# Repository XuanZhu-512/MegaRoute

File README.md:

# MegaRoute — PCB Routing Algorithm Reimplementation

A research and reimplementation project based on **MegaRoute: Universal Automated Large-Scale PCB Routing Method with Adaptive Step-Size Search** (DATE 2025).

## 1. Overview

**当前架构决策（2026-11-16）：** 正式 benchmark 统一输入/输出 `.kicad_pcb`，保留配套项目规则；MegaRoute、Freerouting、KRT 共用锁定版本的外部 KiCad 评测。几何 IR 仅作为自研算法内部接口，提供 KiCad -> IR 和原板模板上的 IR 结果回写契约。当前已落地架构契约、案例快照及版本探测，转换器和正式外部评测仍待实现。详见 [`pcb-bench/docs/ARCHITECTURE.md`](pcb-bench/docs/ARCHITECTURE.md)。下文较早规划中的 JSON 输入与内部 DRC 指标仅用于几何核心开发测试，不再定义跨算法正式评测口径。

This project aims to study, reconstruct, and independently implement the MegaRoute algorithm, a universal automated PCB routing method designed for large-scale printed circuit boards (PCBs).

MegaRoute combines adaptive step-size search, shape-based obstacle detection, and routing optimization to achieve high routing completion rates while maintaining strict Design Rule Check (DRC) compliance.

**Original Paper:**

- **Title:** MegaRoute: Universal Automated Large-Scale PCB Routing Method with Adaptive Step-Size Search
- **Authors:** Haiyun Li, Jixin Zhang
- **Conference:** DATE 2025
- **DOI:** [10.23919/DATE64628.2025.10993225](https://doi.org/10.23919/DATE64628.2025.10993225)
- **IEEE Xplore:** https://ieeexplore.ieee.org/document/10993225

## 2. Research Objectives

- Develop an end-to-end, universal router for entire PCBs, including mainboards with thousands of nets, heterogeneous components, and multiple layers.
- Achieve nearly complete connectivity and DRC-compliant final routing while keeping computation practical at large scale.
- Combine the path-search capability of grid-based routing with precise geometric obstacle modeling, avoiding fixed-grid precision errors and overly restricted search spaces.
- Minimize wire length and via count while maximizing routability. The paper expresses this as `max R(P) - W(P) - V(P)`, subject to `P` satisfying design rules, given layout `L`, netlist `N`, and rules `D`.

For this reimplementation, the objective is to reconstruct and evaluate these mechanisms against the paper's reported results. Differential-pair support is identified as future work in the paper, not an established capability of MegaRoute.

## 3. Algorithm Overview

The workflow is `layout + netlist + design rules -> initialization -> route generation with geometric obstacle detection -> iterative routing optimization -> final routes`

**Adaptive step-size search.** Each net is decomposed into two-terminal searches over nodes `(x, y, z)`, where `z` is the layer. Five exploration operations generate candidates (Figure 4, Equations 2-7):

1. **Obstacle-aware exploration:** expand in eight planar directions. With wire width `w`, nearest-obstacle distance `d`, and parameter `beta`, use step `delta = w` when `d <= beta * w`, otherwise `delta = beta * w`.
2. **Axis alignment:** align with the target along the axis with the smaller absolute displacement, when both coordinate displacements are nonzero.
3. **Diagonal alignment:** adjust one coordinate so the remaining target direction is 45 degrees, when `0 < abs(abs(dx) - abs(dy)) < delta`.
4. **Layer change:** consider nodes at the same planar coordinates on other layers, using vias.
5. **End connection:** connect directly when the target is on the same layer, closer than the step size, and aligned horizontally, vertically, or diagonally.

**Shape-based obstacle detection.** Represent pins as polygons/circles, boundaries and wires as line geometry, and vias as circles. Compute geometric clearances with wire widths and radii included. Same-layer shapes belonging to different nets obstruct one another; boundaries and restricted areas also constrain routing. Each proposed wire is checked against existing geometry, and a via requires clearance checks across the layers it penetrates.

**Routing optimization.** Prioritize candidates using wire-length cost, DRC-violation cost, and layer-change cost. The A*-like length heuristic is `h = max(abs(dx), abs(dy)) + (sqrt(2) - 1) * min(abs(dx), abs(dy))`. Suppress new nodes within `d_min` of an existing node to limit search density. Iterative rerouting increases the DRC penalty using `alpha_i = L * (f(i) - f(0)) / (f(2*mu) - f(0))`, where `f(x) = 1 / (1 + exp(-k*(x-mu)))`.

Intermediate iterations can tolerate violations at a penalty; DRC-free results refer to the reported final outputs. The paper mentions path refinement but does not provide a separate detailed refinement algorithm.

### 3.1 Algorithm Specification（实现前优先冻结）

下文 **[P]** 表示论文明确给出的机制，**[E]** 表示为形成可执行规范而补充的工程约定。工程约定不代表作者实现；所有算法尚待实现。

#### 搜索状态与节点管理

**[P]** 每个网络分解为若干两端路径问题。位置状态为 `n=(x,y,z)`，起点 `s`、终点 `t`，`z` 是铜层索引。令 `dx=t.x-x`、`dy=t.y-y`、`a=abs(dx)`、`b=abs(dy)`、`q=abs(a-b)`。搜索通过当前节点到候选节点的边构成路径。论文规定：新节点距已有节点小于 `d_min` 时抑制新节点。

**[E]** 搜索上下文保存 net ID、线宽、目标、规则、不可变的本次搜索障碍快照；记录保存 `position, heading, g_length, g_drc, g_via, parent, operation, insertion_id`。`heading` 是当前层的八方向入射方向，起点和换层后的第一段为未定。同位置、同层、不同入射方向是不同状态，避免一个到达挡住另一个合法的 45° 到达。每次两端搜索清空 open/closed 和节点索引。候选先执行规则检查，再进行去重/抑制；同位置且同入射方向的较低累计代价可更新并重新入队。密度查询比较同层的所有已采样位置，不按入射方向过滤，条件为欧氏距离 `< d_min`；目标连接不受密度抑制。同一位置的不同入射方向作为同一几何采样点的不同搜索状态保留。这是为转角约束补充的工程状态管理，不是论文给出的完整状态机。队列按 `(F, h, insertion_id)` 升序，同分时固定插入顺序：八方向按东起逆时针、轴对齐、对角对齐、层号升序换层、末端连接。

终点从优先队列弹出后回溯路径；起终点相同直接判为已连接。open 耗尽仅表示在本搜索策略下未找到路径，不证明连续空间不可达。自适应采样和密度抑制不保证完备性或全局最优性。同一层相邻段的转角不超过 45°（内角至少 135°）。过孔不继承上一层的平面入射方向，下一层的第一段重新自由选向。已有同网焊盘或过孔内部的汇接不作为两条独立路径之间的平面转角；纯线段接头仍检查转角。此角度检查是工程补充，论文未给出分支、接入与细化的完整算法。

#### Adaptive Step Size 与五种探索

**[P, Eq. 2]** 当前网络线宽为 `w>0`，最近障碍距离为 `d_obstacle`：

```text
delta = w         if d_obstacle <= beta*w
        beta*w    if d_obstacle >  beta*w
```

它是两档步长，而非随距离连续插值。**[E]** 论文未精确定义该距离的参考点及是否扣除规则间距；首版取当前节点到同层异网实体铜、板边及禁布区的最小几何距离，不扣除当前线宽半径或 clearance，位于障碍内部时为 0，无障碍时为正无穷。该距离仅控制采样密度，不能替代整段 DRC。记录为 `obstacle_distance_mode=point_to_shape`。

| 探索 | 数学规则 [P] | 前提及实现注意 |
| --- | --- | --- |
| Obstacle-aware，Eq. 3 | `{(x+u,y+v,z) : (u,v) in {-delta,0,delta}², (u,v)!=(0,0)}` | 共八个候选；对角边长度为 `sqrt(2)*delta`，不是 `delta` |
| Axis alignment，Eq. 4 | `a<b` 时 `(x+dx,y,z)`；否则 `(x,y+dy,z)` | 仅当 `a>0 AND b>0`；相等时走 y 分支；论文没有要求该对齐边短于 delta |
| Diagonal alignment，Eq. 5 | `a<b` 时 `(x,y+q*sign(dy),z)`；`b<a` 时 `(x+q*sign(dx),y,z)` | 仅当 `0<q<delta`；调整后到目标的剩余方向为 45° |
| Layer change，Eq. 6 | `{(x,y,z') : z' in Z, z'!=z}` | 候选包括所有其它铜层；[E] 再按允许过孔类型和实际贯穿层筛选，不能默认只检查起止层 |
| End connection，Eq. 7 | 候选为 `t`：`dy=0` 时 `(x+dx,y,z)`；`dx=0` 时 `(x,y+dy,z)`；`a=b` 时 `(x+dx,y+dy,z)` | 要求 `z=t.z`、距离 `<delta`，且满足上述方向之一；[E] 距离采用 `sqrt(dx²+dy²)`，原文未明确范数 |

**[E]** 以上是候选生成规则，不保证候选可接受。所有平面候选，包括长轴对齐边，都要检查整条带宽线段；换层检查完整过孔。相等判断使用几何容差，候选落到目标时使用目标的原始坐标，不累积舍入误差。

#### Heuristic 与 Cost Function

**[P, Eq. 8]** 长度代价由起点到当前节点的历史线长与目标估计距离组成：

```text
h(n,t) = max(a,b) + (sqrt(2)-1)*min(a,b)
```

**[P, IV-C.1]** DRC 代价反映违规数量；换层代价通常与过孔直径成正比。论文没有给出三者相加的完整公式、单位归一化、权重数值或违规累计规则。

**[E]** 首版冻结以下组合（不是论文原公式），几何仍存 mm，成本长度单位 `u_cost=0.0254 mm`：

```text
g_length = sum(planar_edge_length / u_cost)
g_drc    = sum(number_of_unique_violation_keys_for_each_edge)
g_via    = sum(diameter_of_inserted_via / u_cost)
F_i(n)   = g_length + h(n,t)/u_cost + alpha_i*g_drc + lambda_v*g_via
lambda_v = 1
```

每条边内按 `(rule, obstacle_id, layer)` 去重；跨边重复遇到障碍仍可重复计费，因此此搜索代价不等于最终全板 DRC 数量，也会受路径分段影响。层变不增加平面线长；首版每个层变动作计一次过孔成本，最终物理过孔数另行去重。几何硬约束违规直接拒绝；仅异网铜间距违规可作为软冲突。严格模式下 `g_drc=0`，一切间距违规拒绝。不得通过米/mm 单位切换而无声改变代价权重。

#### Logistic DRC Penalty

**[P, Eq. 9]**

```text
f(x)    = 1 / (1 + exp(-k*(x-mu)))
alpha_i = L * (f(i)-f(0)) / (f(2*mu)-f(0))
L=200, k=0.4, mu=10; maximum iterations=20
```

由公式可得 `alpha_0=0`、`alpha_10=100`、`alpha_20=200`。**[E]** 原文未说明首次迭代编号；首版总共最多 20 次布线遍历，编号 `i=1..20`（`alpha_1` 约为 1.79），不额外运行第 0 轮。迭代中 alpha 固定；跨轮重建搜索状态。迭代参数改变需验证分母非零，并记录实际权重序列；不擅自把公式延伸到 `i>20` 后仍称最大权重为 L。

#### 重布线策略

**[P, IV-C.2]** 论文说明顺序布线会挤占后续网络空间，采用多轮布线，并用 Logistic 逐步增大违规惩罚。没有明确给出拆线集合、网络次序、失败回滚、历史拥塞项或完整伪代码；不能直接将 Pathfinder 的所有机制视为 MegaRoute 已定义内容。

**[E]** 首版采用以下可替换的确定性策略 `reroute_policy=conflict_nets_v1`：

1. 输入已有同网铜先构成连通分量；使用端点欧氏距离的最小生成树分解连接需求，同分按端点 ID；网络按需求总长度降序、net ID 升序排列。焊盘首版采用中心作为搜索接入点，中心须在铜内，非凸形状否则需显式接入点。
2. 第 1 轮布线全部待连接网络。每轮结束独立检查连通性和 DRC；未完成网络及所有冲突涉及的可编辑网络构成下一轮集合。板框、焊盘、固定铜、禁布区不可拆除。
3. 下一轮先同时移除选中网络的全部新增铜并更新索引，再按固定顺序重新生成剩余连接需求、逐个布线；未选网络保留。失败网络不恢复旧违规走线，保留部分成果并记录失败原因。
4. 每轮保存工作快照、最佳零违规快照及最佳诊断快照。合法解按 `(完成连接数降序, WL升序, VC升序)` 比较；诊断解按 `(完成连接数降序, DRC升序, WL升序, VC升序)` 比较。预算用尽返回合法解（可为空的新增路线）及独立标记的诊断解，不混用指标。
5. 全部需求连通且 DRC=0 时提前终止；否则直到 20 轮或预算耗尽。不宣称 Logistic 必然消除所有违规。路径细化默认关闭，后续独立评估。

### 3.2 Geometry & DRC Specification

**[P, IV-B，pp. 4-5]** 引脚用圆或多边形，走线/边界用线几何，过孔用圆；对象关联网络和层。异网且同层对象互为障碍，过孔必须检查其穿越的各层。以下实体定义、容差及检查覆盖范围是 **[E]**，将原文描述补全为平台规范。

#### 数学表示与层跨度

设圆盘 `D(c,r)={p:||p-c||<=r}`，线段 `S(a,b)={a+t(b-a):0<=t<=1}`。

| 对象 | 实体表示与属性 |
| --- | --- |
| 圆焊盘 | `D(c,r)`，net ID、pad ID、铜层集合 |
| 多边形焊盘 | 简单闭合多边形的填充区域 P；内孔显式存储；拒绝自交轮廓 |
| 走线 | 胶囊体 `S(a,b) ⊕ D(0,w/2)`，圆端帽，所属单一铜层；折线为各段实体并集 |
| 过孔 | 中心 c、外铜半径 R、钻孔半径 r、起止层及每层铜形状；间距检测保守使用外圆盘，钻孔与镀层连通属性独立保存 |
| 板框/开孔 | 可布线区域 B（外多边形减内部开孔）；边界为有限线段，不能当无限直线 |
| 禁布区 | 闭合区域 K 和适用铜层集合，与 net 无关；无网络铜按障碍处理，不视为同网 |

铜层 `Z={0,...,m-1}` 按 stackup 排序；丝印、阻焊不参与路由层编号。实体 A、B 仅在 `layers(A) ∩ layers(B)` 上检查铜间距。通孔穿越全部铜层，即使搜索仅从层 0 到层 1 也必须检查其它层；盲埋孔使用真实起止层的连续跨度，只能使用输入允许的 via type。首版生成器只用通孔；未声明的层跨度或 via 类型应报错。平面同网铜相交建立连通关系，跨层只通过明确的镀通孔/过孔连通，不能仅凭 x/y 相同判定连接。

#### Clearance 和精确窄相检查

定义 `dist(A,B)=min ||a-b||`（a、b 属于各自闭合实体）；相交或包含时为 0。规则间距 `c_req>=0` 使用 net-class 对称配对规则，未设置配对规则时取两网要求的较大值。数值容差默认 `eps=1e-6 mm`，与 `d_min=0.0254 mm` 完全独立。

| 对象对 | 几何间距计算（未截断量为负代表重叠） |
| --- | --- |
| 圆-圆 | `g=||c1-c2||-r1-r2` |
| 圆-走线 | `g=dist(c,S)-r-w/2`，投影参数钳制到 `[0,1]`，含端点和退化线段 |
| 走线-走线 | `g=dist(S1,S2)-(w1+w2)/2`，先检查交叉，再求端点到线段距离最小值 |
| 多边形-圆 | `g=dist(c,P)-r`；先执行点在填充区域内判断，不能只测轮廓边 |
| 多边形-走线 | `g=dist(S,P)-w/2`；线段与实体相交/包含时底层距离为 0 |
| 多边形-多边形 | `g=dist(P,Q)`；相交、包含先判为 0，否则取边对距离最小值 |
| 铜-板边/开孔 | 先要求整个铜实体包含于 B，再要求到 `boundary(B)` 的距离不小于板边间距 |
| 铜-禁布区 | 不得与 K 相交；若规则另设退让距离，还需 `dist(copper,K)>=c_keepout` |

铜间距使用 `max(0,g)`，其中负值不作为通用穿透深度。间距 `<c_req-eps` 判违规；落在容差带内记录边界诊断。异网实体相交或接触另报短路，即使 `c_req=0` 也不能仅靠非负距离判合格。同网间距豁免不豁免板边、禁布、线宽、钻孔等约束。数值上无法确定的临界几何应保守拒绝候选并报告，不能默认合法。

实现采用扩张 AABB / R-tree 的宽相过滤后进行上述窄相几何判断；查询框必须覆盖线宽半径和最大相关间距。这里“精确”表示检查实际实体而非栅格占用，并不宣称双精度运算具有任意精度算术保证。最终全板检查独立枚举对象关系，小案例以全量对象对检查对照索引结果，覆盖相切、包含、退化线段、长边穿障碍及过孔中间层冲突。

#### 内部 DRC 覆盖与局限

首版支持：异网铜短路/间距、最小线宽、板边/孔洞间距、禁布区、过孔尺寸/铜环下限 `(R-r)`、合法层跨度及端点连通性。断路独立计入未完成连接，不同时计作几何 DRC。固定输入的违规单列，新增或由新增铜参与的违规另列，总体零违规必须两者皆为零。

首版不支持：差分对、等长/时延、阻抗、信号完整性、回流路径、阻焊/丝印、热焊盘、自动铺铜、钻孔到钻孔/铜的完整制造约束、完整角度规则及厂商专有 DRC。圆弧/样条需后续受控转换或明确拒绝；不能静默离散化后声称原始几何精确。过孔外圆盘模型对孔内铜关系是保守近似。报告必须带 `supported_rules`、`unsupported_features` 和容差；内部 `DRC=0` 只表示受支持规则下通过。论文用 EasyEDA 评价，平台结论须在后续真实数据阶段交叉验证。

## 4. Development Environment

| Item | Reported configuration |
| --- | --- |
| Implementation language | C++ |
| Compiler/toolchain | mingw64 (MinGW64); compiler version and flags not specified |
| Operating system | Windows 11 |
| CPU / RAM | Intel Core i9-13900K / 64 GB |
| Input format | EasyEDA Pro project format; its conversion tool exports inputs for other routers |
| Evaluation tool | EasyEDA; reference [20] identifies EasyEDA Pro Edition 2.1.25 |
| Search parameters | `beta = 5`, `d_min = 1 mil` (0.0254 mm) |
| DRC optimization | `L = 200`, `k = 0.4`, `mu = 10`; maximum 20 iterations |

The paper does not specify a C++ standard, build system, third-party geometry libraries, parallelization settings, or an exact build command. These remain implementation decisions for this project.

**Evaluation dataset:** 101 real-world designs from OSHWHub, spanning 7-1564 nets, 2-6 layers, 14-3161 pins, 6-2326 connections, and 42-37845 mm². There are 93 designs below 1000 pins and 8 designs with 1011-3161 pins. Although the abstract uses broader wording, Section V-A specifies 101 designs for the reported experiment.

## 5. Project Structure

**当前实现入口：** [`pcb-bench/README.md`](pcb-bench/README.md)。代码已放在 `pcb-bench/`，提供 C++17 CLI、标准 JSON、几何/DRC、固定步长与严格 DRC 自适应搜索、测试及 Python 实验工具。下面的目录是完整目标设计；已实现范围、工程差异和待办以子目录 README 为准，Logistic 多轮重布线已接入，默认后端使用 `configs/megaroute.json`。

以下为**待实现的项目设计**，并非已经存在的代码或论文指定的工程结构。仿真平台定位为 PCB 几何布线、DRC 检查和算法实验平台，不包含电磁场或信号完整性仿真。先用合成电路板和手写标准数据跑通流程，再接入真实设计；EasyEDA 文件解析、转换和回写脚本暂不实现。

### 5.1 技术方案与模块边界

- **算法核心：** C++17 + CMake + Ninja，优先支持 Windows / MinGW64；以独立库形式实现几何、搜索、重布线和评估，命令行程序负责组织运行。先保证单线程结果可复现，性能优化依据 profiling 再推进。
- **数据与配置：** 采用版本化 JSON，计划使用 nlohmann/json；几何索引计划使用 Boost.Geometry R-tree，精确距离与碰撞判断封装在独立模块内。依赖版本在搭建阶段锁定，不依赖运行时自动下载。
- **实验与展示：** Python 负责合成案例、批量实验和统计；先用 Matplotlib 展示分层走线、过孔、障碍物及 DRC 标记，通过 JSON/事件日志回放算法过程。展示端读取核心输出，不另写一套布线逻辑；无界面模式也能完成全流程。
- **测试：** CTest + Catch2 验证 C++ 核心，Python 实验工具按需测试。内部 DRC 是平台定义规则下的检查结果，不能直接替代后续 EasyEDA 外部验证。

### 5.2 目标目录

数据统一位于与 `pcb-bench/` 并列的 `dataset/`：`dataset/test/` 存放 KiCad 测试板，`dataset/geometry-fixtures/` 存放内部 JSON 几何夹具。以下为程序模块目标，命令示例从 `pcb-bench/` 执行。

```text
MegaRoute/
├── README.md
├── CMakeLists.txt                 # 核心库、CLI、测试目标
├── CMakePresets.json              # 开发/发布构建配置
├── pyproject.toml                # 实验和可视化工具依赖
├── include/megaroute/            # 对外类型、路由器和适配器接口
├── src/
│   ├── model/                    # Board、Layer、Pad、Net、Rules、Route
│   ├── geometry/                 # 图形距离、碰撞、分层空间索引
│   ├── drc/                      # 候选检查与最终全板检查
│   ├── routing/                  # 两端连接分解、搜索状态、五类扩展、代价
│   ├── optimization/             # 冲突记录、拆线重布、惩罚调度、路径简化
│   ├── simulation/               # 场景生命周期、快照、事件、停止条件
│   ├── evaluation/               # 连通性、线长、过孔、DRC、运行开销
│   └── io/                       # 标准 JSON 读写与适配器契约
├── apps/                         # megaroute_cli 入口
├── schemas/                      # board、config、result、event 的 JSON schema
├── adapters/
│   └── easyeda/                  # 仅接口说明与映射约定；暂不写解析脚本
├── configs/                      # 基线、完整算法、消融、规模实验配置
├── tools/
│   ├── generate_cases/           # 标准格式合成板生成
│   ├── experiments/              # 批量运行、超时管理、汇总
│   └── visualization/            # 分层显示、搜索与重布线回放
├── tests/
│   ├── unit/                     # 几何、规则、候选、代价和惩罚函数
│   ├── integration/              # 输入到最终布线的确定性案例
│   └── fixtures/                 # 合法、非法、不可达及边界条件输入
├── docs/                         # 数据协议、算法映射、复现假设记录
└── results/                      # 每次运行的配置、走线、日志与指标
```

`build/` 和 `results/` 的生成内容不纳入版本控制；小型测试夹具与实验配置纳入版本控制。核心依赖方向为 `CLI / simulation -> routing / optimization -> model / geometry / drc`，评估读取模型和结果；核心不得依赖展示工具或 EasyEDA 数据字段。

### 5.3 标准数据与 EasyEDA 预留接口

标准输入 `BoardDocument` 包含 `schema_version`、单位、板框及开孔、铜层顺序、焊盘形状与所属网络、网络端点、禁布区、固定走线和过孔、线宽/间距/过孔规则。坐标统一为 mm，明确原点和轴方向；内部使用双精度几何并配置数值容差，`d_min` 与数值容差独立，不能将搜索节点抑制等同于固定网格量化。焊盘与过孔必须注明占用层/层跨度。

初期规则覆盖线宽、异网铜间距、板边间距及过孔铜环/孔径/层跨度；未支持的规则或图形必须报告，不能静默丢弃。导入时校验 ID 唯一性、网络引用、层引用、几何合法性和单位。固定输入中的违规项单独记录，避免与新增走线违规混淆。

| 接口契约（计划） | 职责 |
| --- | --- |
| `IBoardImporter.load(path, options) -> ImportResult` | 返回标准板数据、来源 ID 映射、警告及不支持项；当前仅实现标准 JSON importer |
| `IRouter.route(board, config, observer) -> RoutingResult` | 接收与 EDA 无关的模型；返回走线、未完成连接、终止原因和统计 |
| `IRouteExporter.save(result, path, options)` | 当前仅输出标准 JSON；保留未来 EasyEDA 导出扩展点 |
| `IRoutingObserver.on_event(event)` | 记录搜索、提交走线、拆线、迭代完成等事件；支持关闭或采样以控制开销 |

EasyEDA 适配器后续负责单位、层、图形、网络和规则到上述模型的映射；保留 `source_id` 与扩展元数据以便追溯和未来回写。现阶段调用未实现的 EasyEDA 适配器应明确返回 `unsupported_format`，不以空板或模拟成功替代。

一次运行输出 `board.json`（规范化输入）、`config.json`（实际生效参数）、`routes.json`、`metrics.json` 和可选 `events.jsonl`。记录随机种子、代码版本、编译配置、机器信息、输入摘要、时间/内存限制及终止状态。原始输入保持不变，动态走线支持按 net 撤销和重建索引。

## 6. Implementation Roadmap

按下列依赖顺序推进，每阶段达到验收条件后再扩展规模。本文只规划实现，不表示以下命令、接口或功能已经可用。

| 阶段 | 实现内容 | 验收条件 |
| --- | --- | --- |
| P0 工程与协议 | 建立 CMake 核心库、CLI、CTest 和 Python 工具环境；冻结首版 schema、单位和错误协议；预留 EasyEDA 接口 | 干净环境可构建和运行测试；标准 JSON 可往返读取；非法引用、未知版本及未支持格式有明确错误 |
| P1 仿真平台最小闭环 | 实现模型、合成板、场景加载、结果输出和分层可视化；可手动注入路线；建立独立连通性与 DRC 检查入口 | 无需路由算法即可完成“加载 -> 注入 -> 检查 -> 展示”；已知短路、断路、越界和间距违规被准确定位 |
| P2 几何与规则引擎 | 实现圆/多边形焊盘、带宽线段、过孔、板框/开孔、禁布区；按层索引；检查完整线段和过孔穿越层 | 覆盖相切、刚好满足间距、窄缝、斜线、多层过孔；索引结果与小规模暴力检查一致；撤销走线后无残留障碍 |
| P3 基线搜索 | 实现固定步长 A*、八方向搜索、目标连接和合法换层；确定性队列规则、父节点回溯、预算限制；先从两端网络开始 | 单层绕障、多层跨越、不可达案例结果正确；输出可由独立检查入口复核；不可达与超时可区分 |
| P4 MegaRoute 自适应搜索 | 按 Section 3 的五类探索实现候选生成；接入几何最近障碍距离、长度启发式、换层代价和 `d_min` 抑制；保留逐项开关 | 五类探索各有确定性案例；长步不能穿过薄障碍；抑制按层处理且不误删目标连接；与基线比较节点数、运行时间、连通率 |
| P5 多网络与迭代优化 | 引入多端网络分解、网络排序、动态占用、冲突归属、拆线重布和递增 DRC 惩罚；保存最佳合法解及诊断快照 | 构造需重布线的冲突案例；最多 20 轮并支持时间预算；最终全板 DRC 与连通性重算；残余违规不能标成 DRC-free |
| P6 规模与消融实验 | 完成批量运行、失败恢复、性能剖析和结果汇总；再优化空间查询、内存分配与事件记录 | 固定输入/种子可复现；输出逐板及分组指标；完整算法与三组消融共享数据、预算和计时口径；超时/失败不被丢弃 |
| P7 真实数据接入（后续） | 平台稳定后实现 EasyEDA 适配器，并接入可获取且有明确来源的真实板；外部 DRC 交叉验证 | 转换前后网络、层、单位、规则可追溯；外部检查与内部检查差异有记录；当前任务不实现该阶段脚本 |

### 6.1 搜索和重布线实现顺序

1. 将输入模型、固定障碍、动态走线分离；建立分层索引和连接需求集合。先采用确定性的多端网络生成树分解与网络排序，记录为本项目假设；对已有同网铜连通分量进行合并，避免重复计数和布线。
2. 从固定步长基线开始，再替换候选生成器为障碍感知步长、轴向对齐、对角对齐、换层和末端连接。队列优先级、同分排序、去重、节点抑制与预算均可追踪；每个候选验证完整几何，不只验证终点。
3. 将约束分为不可放宽的边界/层合法性/禁布约束和明确配置的可惩罚铜冲突。软约束模式保留冲突对象与违规量，不允许直接提交为最终合格结果；初期基线使用严格模式。
4. 实现长度、违规和换层代价及 sigmoid 惩罚调度；初始实验采用 README Section 4 的参数。代价权重、违规量定义、距离单位与迭代下标必须写入配置和假设记录，避免把自行补全的细节当作论文原实现。
5. 每轮定位受冲突影响的网络，撤销其动态铜、更新索引并重布；分别保存最佳合法结果和诊断候选。优先比较连通性，再比较线长与过孔；达到全部连接且无违规、迭代上限或资源预算时停止。超时返回部分结果与未完成原因。
6. 最后加入保持连通性和 DRC 的共线合并、冗余段/过孔消除等可选后处理；每次修改后复核。这属于项目补充方案，论文未给出完整路径细化算法，应独立开关和评价。

### 6.2 实验与验收口径

- **场景递进：** 空板两端连接 -> 单障碍/窄通道 -> 多网络争用 -> 多层过孔 -> 多端网络 -> 随机密集板 -> 真实大规模板。所有随机案例保存生成参数和种子；合成规模扫描覆盖 2/4/6 层及不同引脚、网络和障碍密度，不将合成结果称为论文数据集复现。
- **最终验证：** 由独立于搜索提交逻辑的全板检查入口重新计算电气连通性及 DRC；小案例用暴力几何检查校验空间索引。即使连接完成，存在违规时仍应报告 `completed_with_violations`；同时区分合法完成、部分完成、超时和输入错误。
- **计量：** 保存连接数分子/分母、完全连通网络数、违规类型/数量、总线长、唯一物理过孔数、节点扩展量、峰值内存和耗时。连接完成数由实际铜连通性验证，不直接使用搜索成功次数；零连接和零已布连接时的比率标为不适用。分别记录加载、路由、最终检查和展示耗时。
- **消融：** 对比固定 `1 mil` 步长、关闭代价引导、关闭 DRC 最小化与完整算法。明确关闭项保留哪些行为，例如关闭 DRC 最小化仍执行最终 DRC 检查；其它配置不变，记录与论文未明确细节有关的解释。
- **可比性：** 按 `<1000 pins` 与 `>=1000 pins` 分组，同时保留逐板结果及聚合公式；真实大板实验记录 24 小时限制。只在相同连通性和规则条件下比较线长与过孔，论文数字作为参考而非验收承诺。

平台建成后计划提供如下入口（当前不可执行）：

```text
cmake --preset dev
cmake --build --preset dev
ctest --preset dev
megaroute_cli validate --board ../dataset/geometry-fixtures/two_net.json
megaroute_cli route --board ../dataset/geometry-fixtures/two_net.json --config configs/megaroute.json --out results/demo
megaroute_cli check --board results/demo/board.json --routes results/demo/routes.json
```

**第一交付目标为 P0-P3：** 在不依赖 EasyEDA 的情况下，完成合成板输入、可视化、基线布线、DRC 和指标输出的可重复闭环。随后 P4-P6 实现与评估 MegaRoute；`docs/` 持续记录论文机制到代码模块的映射，以及网络分解、排序、代价细节、重布策略和路径细化等复现假设。

### 6.3 Reproduction & Experiment Protocol

本节所有配置为待实现协议。来源：[P] 论文 V-A/C/F（pp. 5-6）；[E] 本项目约定。实验开始前保存完整配置，实验后不得为某个方法单独改参数而保留同一实验名称。

#### 论文机制与工程假设登记

| 内容 | 论文明确部分 [P] | 本项目补全 [E] |
| --- | --- | --- |
| 搜索 | 三维位置、五类探索、Eq. 2-8、节点密度抑制 | 障碍距离参考点、末端距离范数、容差、队列排序、密度例外、入射方向状态、同方向密度抑制 |
| 成本 | 历史长度+启发式、违规数量、与直径有关的换层成本 | 完整加权公式、mil 成本单位、lambda_v、违规累计方式 |
| 优化 | 多轮布线、Logistic Eq. 9 及参数、最多 20 轮 | 首轮编号、网络/连接排序、拆线对象、回滚和最佳解管理 |
| 几何 | 对象类型、距离计算、同层异网和过孔跨层检查 | 实体包含、数值鲁棒性、规则覆盖和过孔类型模型 |
| 消融 | 固定 1 mil、去掉 Cost Guidance、去掉 DRC Minimization | 后两者的精确开关语义，论文未提供消融代码 |
| 评估 | 101 板、两组规模、指标名称、大板 24 小时限制 | 合成数据、重复次数、聚合公式、内存/节点预算及超时处理 |

假设按配置字段与版本记录在 `docs/`，任何改变都生成新的实验 ID。不能以“实现完成”代替“复现成功”；未获取原始 101 板清单和完全相同规则时，只能称机制复现与独立评估。

#### Baseline 与 Ablation 配置矩阵

共同配置：[P] `beta=5, d_min=0.0254 mm, L=200, k=0.4, mu=10`；[E] `lambda_v=1, u_cost=0.0254 mm, eps=1e-6 mm`，单线程、固定排序、路径细化关闭、通孔默认外径 0.6 mm / 孔径 0.3 mm（仅合成板；真实板遵循自身规则）。固定步长仅替换 Eq. 2；四种辅助候选仍保留，以控制变量。它不是对 Freerouting 或论文其他工具的重实现。

| 配置 ID | 步长与候选 | 搜索优先级 | DRC/重布线策略 |
| --- | --- | --- | --- |
| `baseline_fixed_strict` [E] | 固定 1 mil，保留五类候选 | `g_length+h/u_cost+lambda_v*g_via` | 严格 DRC、单次顺序遍历；作为平台基线，不是论文 Table II 的单项消融 |
| `megaroute_full` | 自适应步长、五类候选 | Section 3.1 的 `F_i` | 可惩罚异网间距、Logistic、最多 20 轮 |
| `ablation_fixed_step` | 仅将 delta 固定为 1 mil | 与 full 相同 | 与 full 相同 |
| `ablation_no_cost_guidance` | 与 full 相同 | [E] FIFO，固定候选顺序，不用 F 选择扩展节点 | 保留冲突检测、迭代和拆线；alpha 仍记录但不影响 FIFO，因此此消融也失去罚权对节点优先级的影响 |
| `ablation_no_drc_minimization` | 与 full 相同 | [E] 使用严格模式下的长度+换层成本 | 严格 DRC、仅一轮，不拆线重布；不是将 alpha 设为 0 并允许最终短路 |

后两种消融只是本项目对论文名称的明确解释，不能保证与作者代码相同；报告须保留该说明。每种模式均使用相同的最终独立检查器、相同输入和资源上限。`baseline_fixed_strict` 同时关闭两个机制，不能拿它的差值归因于单一机制。

#### 数据集生成与冻结规则 [E]

1. **确定性正确性集：** 分别建立空板、水平/对角目标、轴距离相等、`q=delta`、距离恰等于 delta、窄通道、包含关系、长步穿薄障碍、过孔中间层冲突、多端网络、固定铜、不可达、输入自带违规等案例；每例标注预期连接与违规，不依赖随机采样。
2. **规模矩阵：** `layers ∈ {2,4,6}`、两端网络数 `N ∈ {20,100,600}`、方板边长 `S ∈ {50,100} mm`、禁布面积比例 `rho ∈ {0,0.1}`；每组合使用种子 `0..9`，共 360 板。种子 `0..4` 用于开发，`5..9` 冻结为评估集，调参后不回看评估结果继续调参。另用固定夹具覆盖多端网络，避免声称本矩阵代表全部真实板特征。
3. **生成规则：** 使用固定版本 NumPy PCG64，记录版本、seed 与 schema；按 x 再 y 抽样中心坐标，均匀分布于 `[1,S-1]²` mm。生成 `2N` 个半径 0.3 mm 圆焊盘，各在顶层/底层中等概率选择；线宽 0.2 mm、铜间距及板边间距 0.2 mm、过孔尺寸见上表。按全层几何排斥放置焊盘，保证中心距至少 0.8 mm，预留区内不得放置。
4. **障碍与连线：** `rho=0.1` 时在板中心放置跨所有铜层的正方形禁布区，边长 `S*sqrt(rho)`；rho=0 时无禁布区。放置完成后用同一 RNG 打乱焊盘 ID，按相邻 ID 配成 N 个两端网络。禁止先布线成功再决定是否接纳案例，生成集不保证可布通。
5. **失败与追溯：** 每板最多尝试 `10000*N` 次焊盘采样，超限记录 `generation_failed`，不通过更换种子隐藏失败。记录所有生成参数、失败数、板面积、层/网络/引脚数、输入 SHA-256；冻结后各方法读取完全相同 JSON。合成数据不套用论文 98% 的验收目标。
6. **真实数据：** 后续清单记录来源 URL、获取日期、文件哈希、规则、许可证、转换器版本、排除原因及固定铜处理方式；不得假设 OSHWHub 任意 101 个设计就是论文原集。EasyEDA 暂留接口，不开发处理脚本。

#### 运行预算与可复现记录

| 项目 | 首版实验约定 [E，注明例外] |
| --- | --- |
| 单板墙钟预算 | 正确性集 60 秒；规模矩阵每种方法每板 3600 秒；真实大板 86400 秒（24 小时为论文设置 [P]） |
| 搜索资源 | 单次两端搜索最多扩展 1,000,000 节点；进程内存上限 8 GiB；单线程；达到限制记录具体原因，不记作已证明不可达 |
| 迭代预算 | full 与对应消融最多 20 轮，严格单轮配置 1 轮；预算从规范化输入加载后开始，包含初始化、布线及轮间检查；最终验证另计时 |
| 重复运行 | 每板每配置 3 次独立进程，关闭事件详录；报告时间中位数及范围，几何结果哈希应相同；若不同，保留全部结果并调查非确定性 |
| 环境 | 保存 CPU/RAM/OS、编译器版本、Release 编译选项、依赖版本、git commit 与工作区差异摘要；不同时运行其它基准任务 |
| 中止与恢复 | 超时/内存/节点上限/崩溃单独记录；按轮写快照；已完成实验可跳过，恢复到半途继续运行的结果另标记，不混入冷启动耗时 |

资源上限是本地评估选择，不是论文参数。最终检查若无法完成，结果为 `validation_incomplete`，不得报告 DRC=0。可增加其它预算档，但同一对照组必须共享上限且分别汇总。

#### 指标的可计算定义 [E，指标名称承接论文]

- **连接需求：** 输入固定铜连通分量经固定 MST 得到不可变的需求端点对清单 Q；`C_total=|Q|`。最终对同网实体做跨层连通性检查，Q 中两端在同一连通分量内即计一次 `C_routed`，禁止通过异网短路获得连通性；另报短路和违规数。此口径是项目约定，未验证与 EasyEDA 的连接计数完全一致。
- **Routability：** `R=C_routed/C_total`；同时报告全部端点连通的网络数/需布线网络数。若 `C_total=0`，R 为 null（不适用），不强填 1。
- **DRC：** 铜对象对按 `(rule, min(object_id), max(object_id), layer)` 去重，单对象违规按 `(rule, object_id, layer)` 去重；同一异网接触只计 short，不再重复计 clearance。一个对象对同层多处违规计一项，跨层分别计数。保存位置、测量值及规则阈值。对象分段可能影响数量，需固定规范化流程；该数值不保证等同 EasyEDA 报告条数。
- **WL：** 新增铜走线中心线总长，`sum(sqrt((x2-x1)^2+(y2-y1)^2))`，含未完成网络的已提交线段；同网同层完全重叠/共线重叠部分先规范化合并，不重复计数。过孔竖直长度不计入 WL，固定输入铜的线长单列。
- **VC：** 新增物理过孔数量，以中心、实际层跨度、类型与网络规范化去重，不能按穿越层数或搜索层变边数直接计数。固定已有过孔单列。
- **meanWL / meanVC：** 分别为 `WL/C_routed`、`VC/C_routed`；`C_routed=0` 时为 null，仍保留 WL/VC。这是项目明确采用的总量比值口径，不能由 Table I 的分组均值反推逐板定义。
- **时间与资源：** 使用单调墙钟分别记录 load、init、route（含轮间检查）、final_check、export；总流水线时间为上述之和，绘图不计入路由。论文只写 total routing time，比较时须注明计时边界差异。另报扩展节点量、峰值内存及终止原因。
- **汇总：** 逐板保存全部原始数值，再按 `<1000` / `>=1000` pins 分组；主报告采用逐板 R 的算术平均，另报 `sum(C_routed)/sum(C_total)` 加权值，二者不混用。WL、VC、meanWL、meanVC 报告逐板均值并注明 null 排除数量；时间采用每板三次中位数再做组均值。论文没有充分说明所有聚合细节，不强称该口径完全一致。
- **失败与超时：** 使用可验证的预算内最佳合法快照计算部分指标，无快照则注明缺失，不静默删样本；诊断快照另表展示。超时的运行时间属于截尾数据，单列超时率/失败率及截尾耗时，成功样本耗时均值必须注明样本数。任何线长/过孔改善都同时给出 R 与 DRC，避免因漏连而显得更优。

## 7. Evaluation Metrics

The paper evaluates metrics using EasyEDA. This project's initial internal evaluation follows Section 6.3; external EasyEDA validation is deferred. Let `C_routed` be the number of successfully routed connections and `C_total` the number of required connections.

| Metric | Definition | Desired direction |
| --- | --- | --- |
| Routability | `C_routed / C_total`; connection-based, not the fraction of fully routed nets | Higher |
| DRC | Number of design-rule violations in the routing result | Zero |
| WL | Total wire length (mm) | Lower, with comparable connectivity |
| VC | Total via count | Lower, with comparable connectivity |
| meanWL | Wire length per routed connection (mm/connection) | Lower |
| meanVC | Via count per routed connection | Lower |
| Runtime | Total routing time; reported in minutes | Lower |

Interpret length and via metrics together with routability: incomplete routing can appear cheaper simply because fewer connections were completed. Large-PCB experiments impose a 24-hour runtime limit; timed-out runs should be marked explicitly.

**Published reference results, not results of this repository** (Table I, PDF p. 6):

| MegaRoute group | Routability | DRC | meanWL (mm) | meanVC | WL (mm) | VC | Runtime (min) |
| --- | --- | --- | --- | --- | --- | --- | --- |
| Pin count < 1000 | 0.9885 | 0 | 9.4917 | 0.4609 | 2718.5300 | 133 | 3.0827 |
| Pin count >= 1000 | 0.9943 | 0 | 11.2119 | 0.4151 | 10493.3533 | 453 | 46.3188 |

These are grouped results; they should not be interpreted as per-board guarantees. MegaRoute is slower than Allegro X and Altium Designer on the large-board group, despite its stronger reported routability and DRC compliance.

The eight comparison methods are Altium Designer, Allegro X, ELECTRA, EasyEDA, Freerouting, FanoutNet, Lin's algorithm, and He's algorithm. The authors reimplemented the last two because their implementations were unavailable.

**Ablation reference results** (Table II, PDF p. 6; reported averages across all cases):

| Configuration | Routability | Runtime (min) |
| --- | --- | --- |
| Without adaptive step-size (`delta = 1 mil`) | 0.9861 | 12.3002 |
| Without cost guidance | 0.9747 | 10.7732 |
| Without DRC minimization | 0.9092 | 1.3748 |
| Full MegaRoute | 0.9890 | 6.5073 |

Reproduction should report both scale groups and the three ablations, retaining per-board measurements and documenting aggregation. The paper does not fully specify the aggregation procedure for every metric in Table I.

## 8. References

1. Li, H., and Zhang, J. *MegaRoute: Universal Automated Large-Scale PCB Routing Method with Adaptive Step-Size Search*. DATE 2025.
2. Hart, P. E., Nilsson, N. J., and Raphael, B. *A Formal Basis for the Heuristic Determination of Minimum Cost Paths*. IEEE Transactions on Systems Science and Cybernetics, 1968.
3. McMurchie, L., and Ebeling, C. *Pathfinder: A Negotiation-Based Performance-Driven Router for FPGAs*. FPGA, 1995.

---

**Project Status:** Initial simulation and strict-routing prototype in `pcb-bench/`; full MegaRoute negotiation and large-scale reproduction remain in progress.

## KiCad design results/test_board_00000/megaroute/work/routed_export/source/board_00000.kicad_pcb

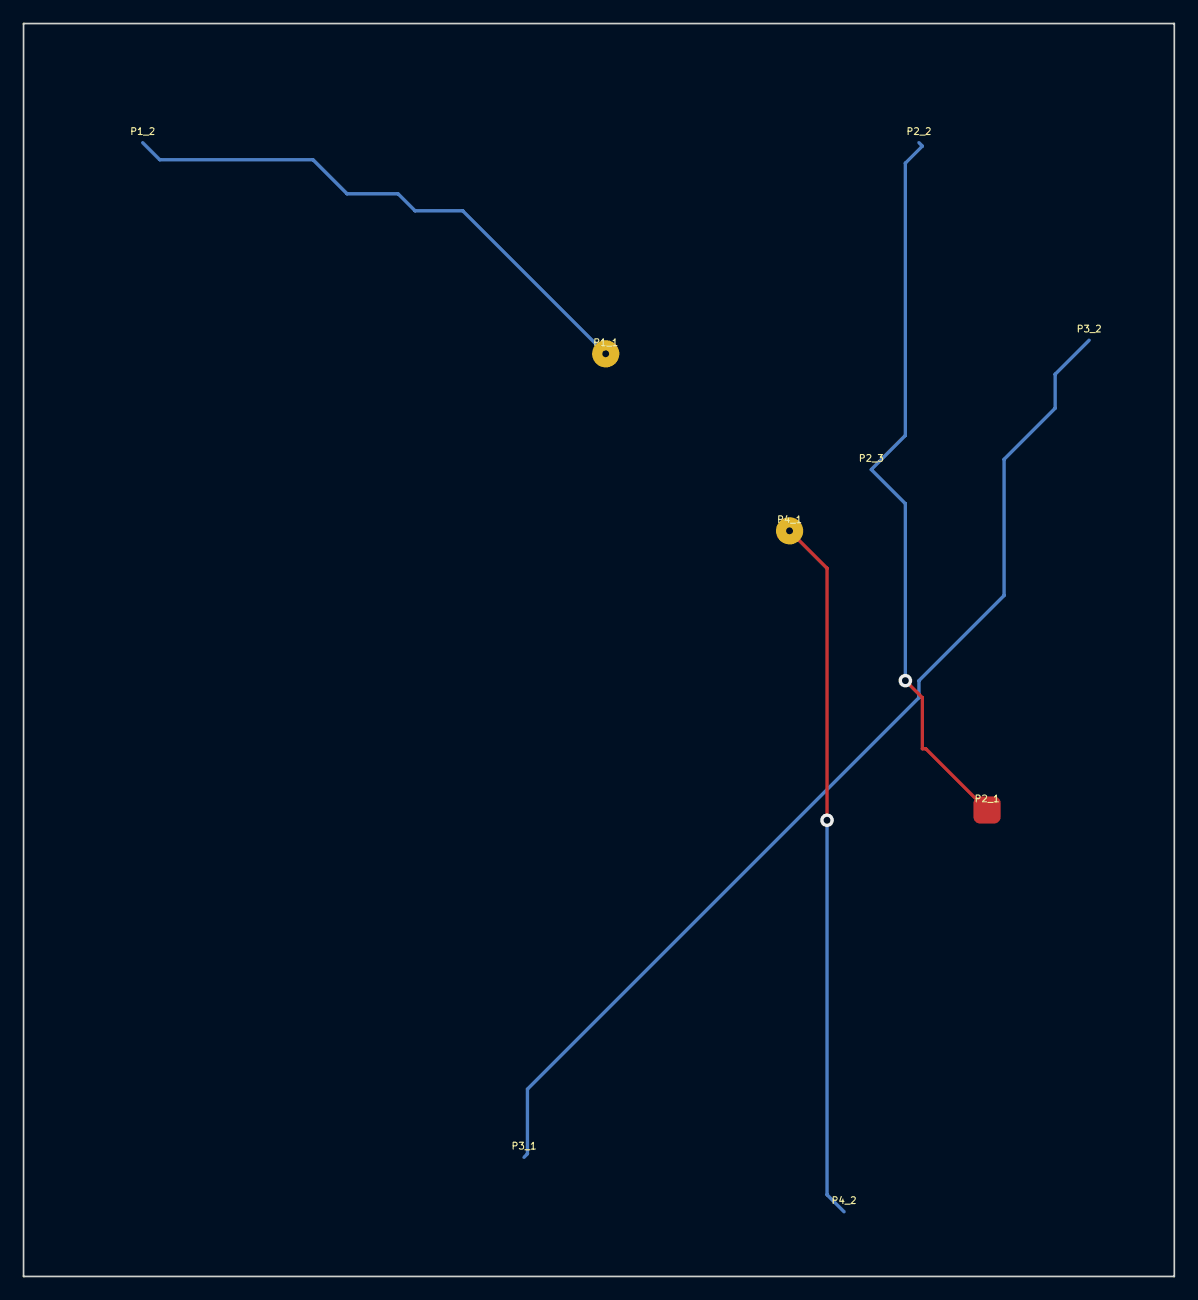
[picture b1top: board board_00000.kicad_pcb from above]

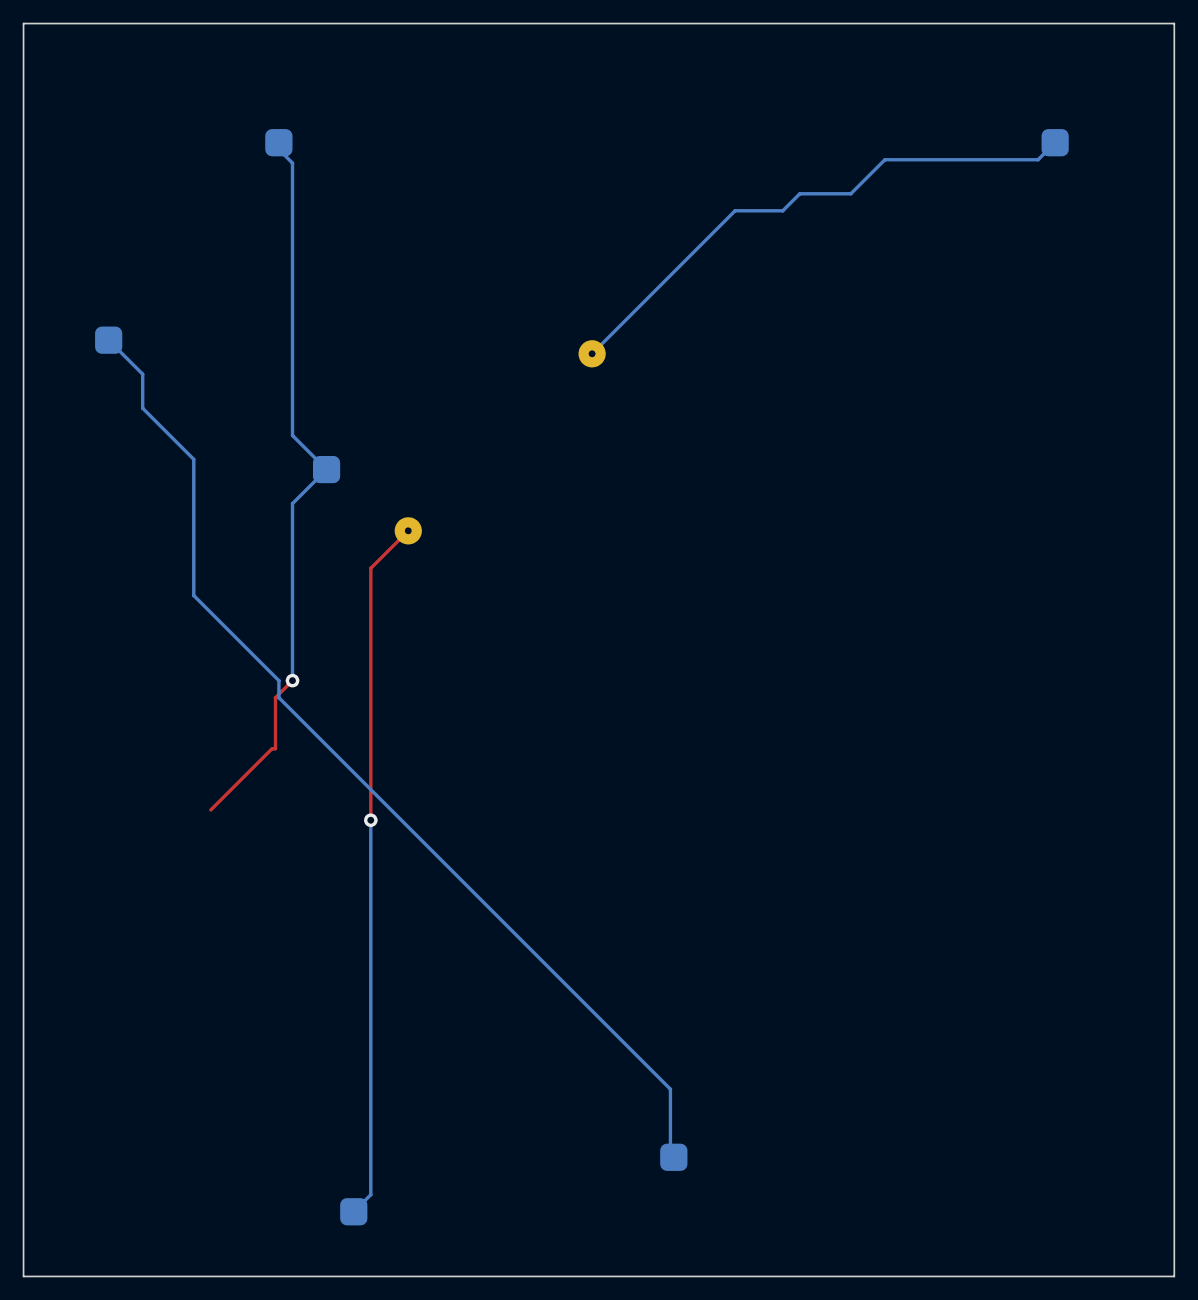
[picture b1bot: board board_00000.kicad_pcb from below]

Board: 2 copper layers, 101.4 x 110.4 mm, 9 parts (6 on the bottom side), 4 nets.

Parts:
P1_1, P4_1: Pad1; PTH
P1_2, P2_2, P3_2, P4_2: Pad2; BCu
P2_1: Pad1; FCu
P2_3: Pad3; BCu
P3_1: Pad1; BCu

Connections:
NET1: P1_1.1, P1_2.1
NET2: P2_1.1, P2_2.1, P2_3.1
NET3: P3_1.1, P3_2.1
NET4: P4_1.1, P4_2.1
